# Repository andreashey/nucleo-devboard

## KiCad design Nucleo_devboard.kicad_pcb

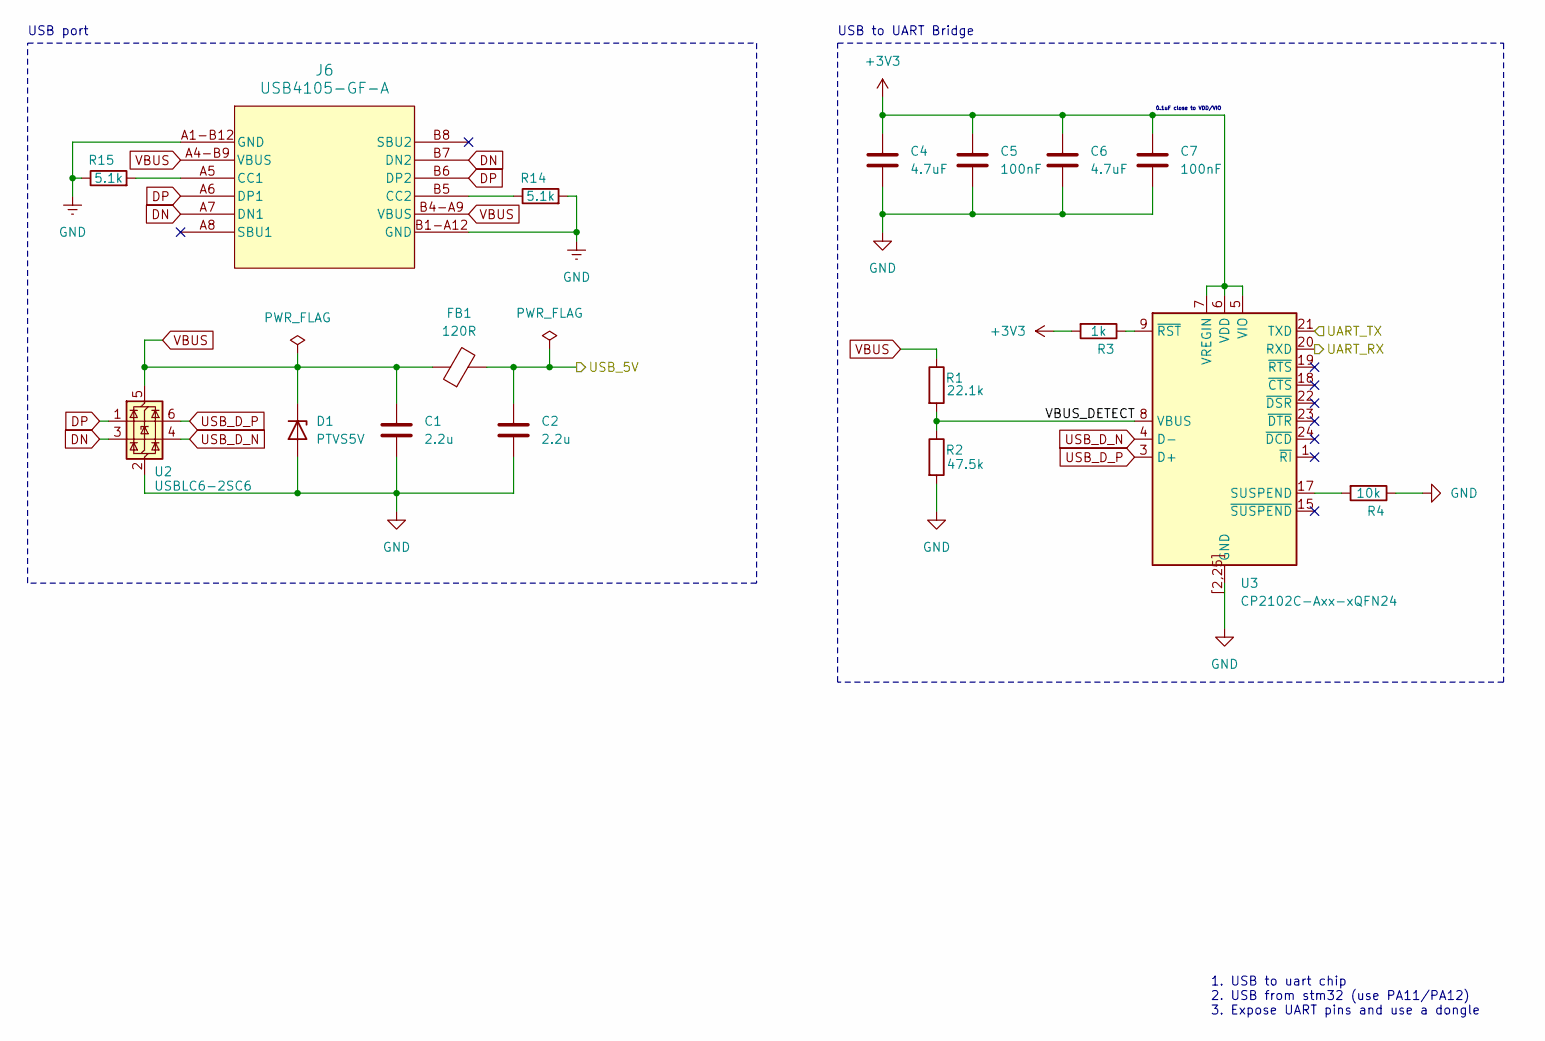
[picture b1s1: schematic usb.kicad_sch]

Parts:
C1, C2: 2.2u; C_0805_2012Metric
C4, C6: 4.7uF; C_0805_2012Metric
C5, C7: 100nF; C_0603_1608Metric
D1: PTVS5V; D_SOD-123
FB1: 120R; L_0805_2012Metric
J6: USB4105-GF-A; USB4105_GCT
R1: 22.1k; R_0603_1608Metric
R2: 47.5k; R_0603_1608Metric
R3: 1k; R_0805_2012Metric
R4: 10k; R_0805_2012Metric
R14, R15: 5.1k; R_0603_1608Metric
U2: USBLC6-2SC6; SOT-23-6
U3: CP2102C-Axx-xQFN24; WQFN-24-1EP_4x4mm_P0.5mm_EP2.45x2.45mm

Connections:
+3V3: C4.1, C5.1, C6.1, C7.1, R3.2, U3.5 (VIO), U3.6 (VDD), U3.7 (VREGIN); also elsewhere on the board
/MCU 1/USART3_RX: U3.20 (RXD); also elsewhere on the board
/MCU 1/USART3_TX: U3.21 (TXD); also elsewhere on the board
/Power/USB_5V: C2.1, FB1.2; also elsewhere on the board
/USB/VBUS_DETECT: R1.2, R2.1, U3.8 (VBUS)
DN: J6.A7 (DN1), J6.B7 (DN2), U2.3 (I/O2)
DP: J6.A6 (DP1), J6.B6 (DP2), U2.1 (I/O1)
GND: C1.2, C2.2, C4.2, C5.2, C6.2, C7.2, D1.2 (A), J6.A1-B12 (GND), J6.B1-A12 (GND), R2.2, R4.1, R14.2, R15.1, U2.2 (GND), U3.2 (GND), U3.25 (GND), U3.[2,25] (GND); also elsewhere on the board
unnamed: J6.A5 (CC1), R15.2
unnamed: J6.B5 (CC2), R14.1
unnamed: R4.2, U3.17 (SUSPEND)
unnamed: R3.1, U3.9 (~RST)
USB_D_N: U2.4 (I/O2), U3.4 (D-)
USB_D_P: U2.6 (I/O1), U3.3 (D+)
VBUS: C1.1, D1.1 (K), FB1.1, J6.A4-B9 (VBUS), J6.B4-A9 (VBUS), R1.1, U2.5 (VBUS)

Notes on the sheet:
1. USB to uart chip 2. USB from stm32 (use PA11/PA12) 3. Expose UART pins and use a dongle
USB to UART Bridge
USB port
0.1uF close to VDD/VIO

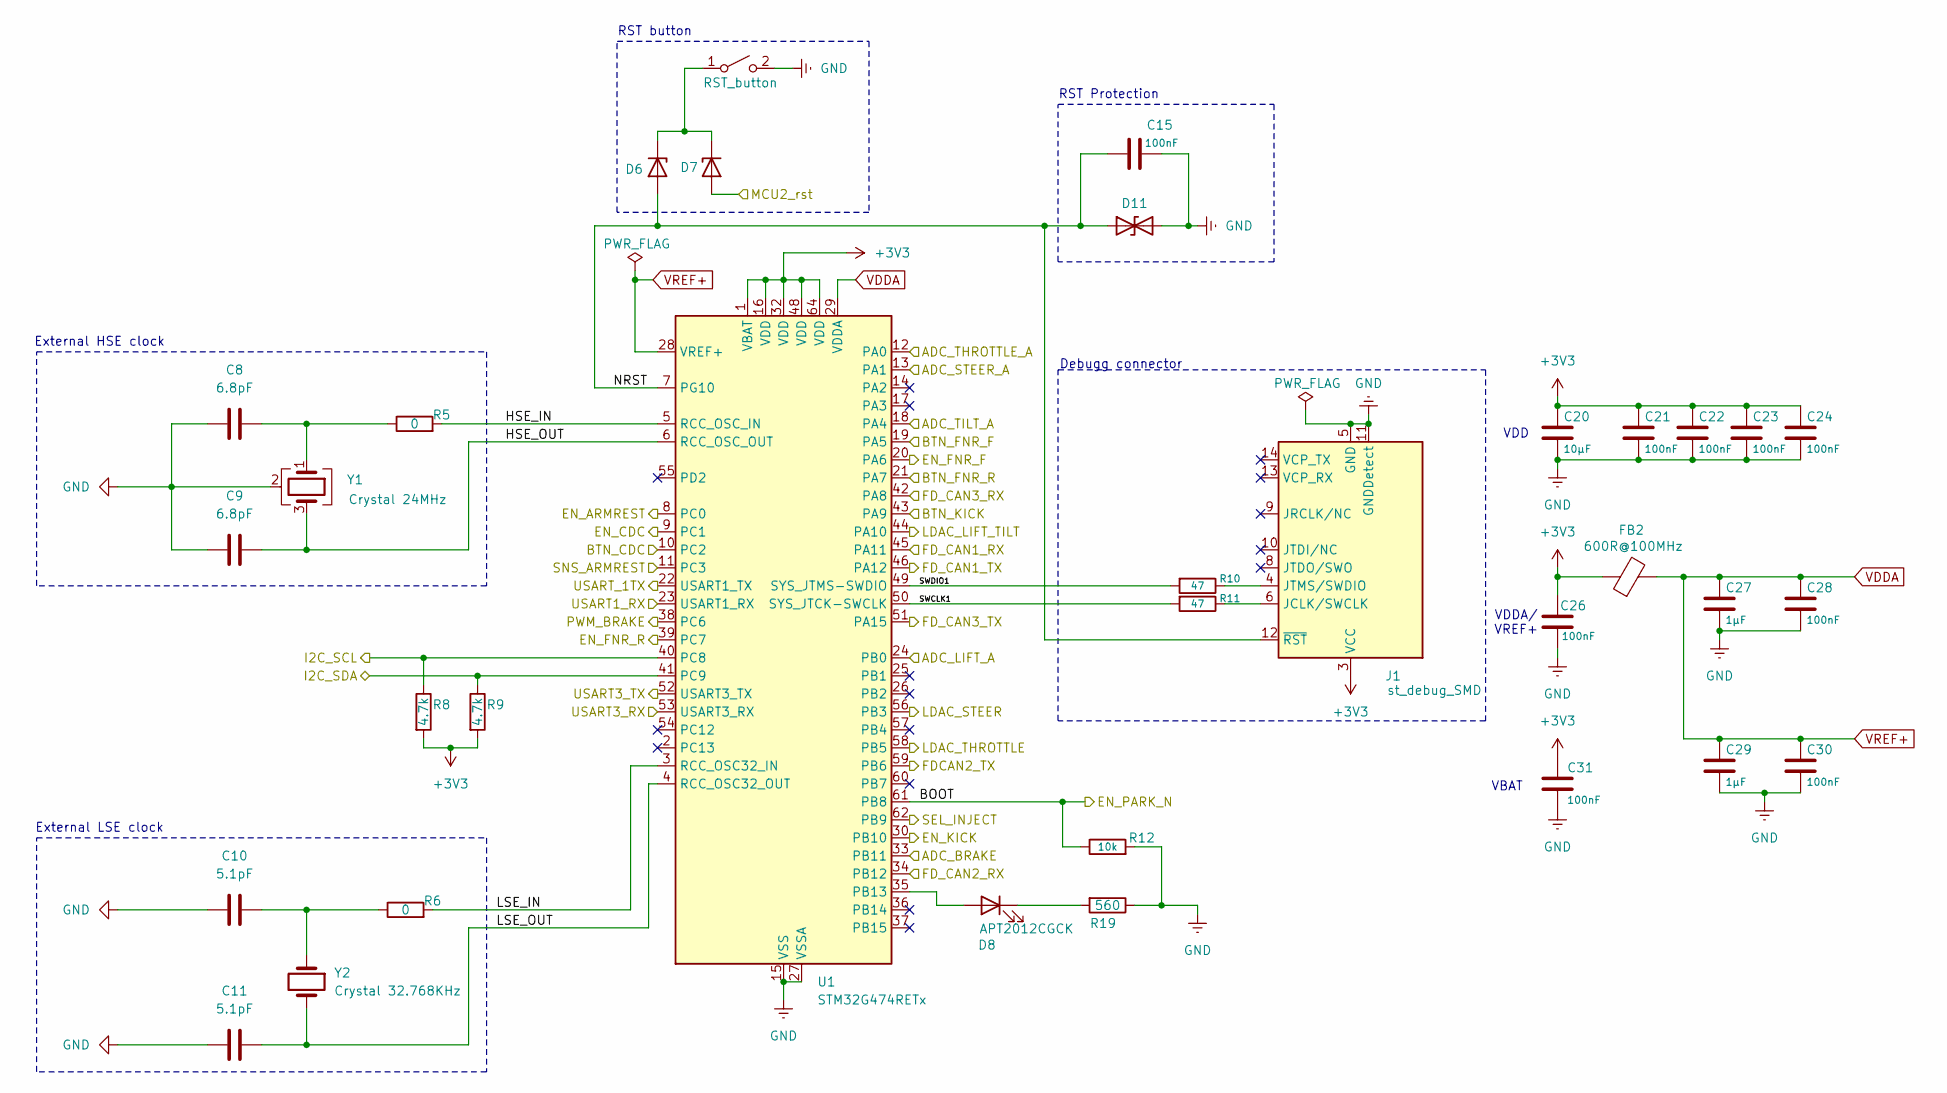
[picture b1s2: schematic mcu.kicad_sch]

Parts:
C8, C9: 6.8pF; C_0402_1005Metric
C10, C11: 5.1pF; C_0402_1005Metric
C15, C21, C22, C23, C24, C26, C28, C30, C31: 100nF; C_0603_1608Metric
C20: 10μF; C_1206_3216Metric
C27, C29: 1μF; C_0603_1608Metric
D6, D7: BAT60A; D_SOD-323
D8: APT2012CGCK; LED_0805_2012Metric
D11: STS321033B401; D_SOD-323
FB2: 600R@100MHz; L_0603_1608Metric
J1: st_debug_SMD; PinHeader_2x07_P1.27mm_Vertical_SMD
R5, R6: 0; R_0603_1608Metric
R8, R9: 4.7k; R_0805_2012Metric
R10, R11: 47; R_0603_1608Metric
R12: 10k; R_0805_2012Metric
R19: 560; R_0805_2012Metric
RESET1: RST_button; SW_TH_Tactile_Omron_B3F-100x
U1: STM32G474RETx; LQFP-64_10x10mm_P0.5mm
Y1: Crystal 24MHz; Crystal_SMD_2016-4Pin_2.0x1.6mm
Y2: Crystal 32.768KHz; Crystal_SMD_3215-2Pin_3.2x1.5mm

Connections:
+3V3: C20.1, C21.1, C22.1, C23.1, C24.1, C26.1, C31.1, FB2.1, J1.3 (VCC), R8.2, R9.2, U1.1 (VBAT), U1.16 (VDD), U1.32 (VDD), U1.48 (VDD), U1.64 (VDD); also elsewhere on the board
/MCU 1/ADC_BRAKE: U1.33 (PB11); also elsewhere on the board
/MCU 1/ADC_LIFT_A: U1.24 (PB0); also elsewhere on the board
/MCU 1/ADC_STEER_A: U1.13 (PA1); also elsewhere on the board
/MCU 1/ADC_THROTTLE_A: U1.12 (PA0); also elsewhere on the board
/MCU 1/ADC_TILT_A: U1.18 (PA4); also elsewhere on the board
/MCU 1/BOOT: R12.1, U1.61 (PB8); also elsewhere on the board
/MCU 1/BTN_CDC: U1.10 (PC2); also elsewhere on the board
/MCU 1/BTN_FNR_F: U1.19 (PA5); also elsewhere on the board
/MCU 1/BTN_FNR_R: U1.21 (PA7); also elsewhere on the board
/MCU 1/BTN_KICK: U1.43 (PA9); also elsewhere on the board
/MCU 1/EN_ARMREST: U1.8 (PC0); also elsewhere on the board
/MCU 1/EN_CDC: U1.9 (PC1); also elsewhere on the board
/MCU 1/EN_FNR_F: U1.20 (PA6); also elsewhere on the board
/MCU 1/EN_FNR_R: U1.39 (PC7); also elsewhere on the board
/MCU 1/EN_KICK: U1.30 (PB10); also elsewhere on the board
/MCU 1/FDCAN2_TX: U1.59 (PB6); also elsewhere on the board
/MCU 1/FD_CAN1_RX: U1.45 (PA11); also elsewhere on the board
/MCU 1/FD_CAN1_TX: U1.46 (PA12); also elsewhere on the board
/MCU 1/FD_CAN2_RX: U1.34 (PB12); also elsewhere on the board
/MCU 1/FD_CAN3_RX: U1.42 (PA8); also elsewhere on the board
/MCU 1/FD_CAN3_TX: U1.51 (PA15); also elsewhere on the board
/MCU 1/HSE_IN: R5.2, U1.5 (RCC_OSC_IN)
/MCU 1/HSE_OUT: C9.2, U1.6 (RCC_OSC_OUT), Y1.3
/MCU 1/I2C_SCL: R8.1, U1.40 (PC8); also elsewhere on the board
/MCU 1/I2C_SDA: R9.1, U1.41 (PC9); also elsewhere on the board
/MCU 1/LDAC_LIFT_TILT: U1.44 (PA10); also elsewhere on the board
/MCU 1/LDAC_STEER: U1.56 (PB3); also elsewhere on the board
/MCU 1/LDAC_THROTTLE: U1.58 (PB5); also elsewhere on the board
/MCU 1/LSE_IN: R6.2, U1.3 (RCC_OSC32_IN)
/MCU 1/LSE_OUT: C11.2, U1.4 (RCC_OSC32_OUT), Y2.2
/MCU 1/NRST: C15.1, D6.2 (A), D11.1 (A1), J1.12 (~RST), U1.7 (PG10)
/MCU 1/PWM_BRAKE: U1.38 (PC6); also elsewhere on the board
/MCU 1/SEL_INJECT: U1.62 (PB9); also elsewhere on the board
/MCU 1/SNS_ARMREST: U1.11 (PC3); also elsewhere on the board
/MCU 1/SWCLK1: R11.2, U1.50 (SYS_JTCK-SWCLK)
/MCU 1/SWDIO1: R10.2, U1.49 (SYS_JTMS-SWDIO)
/MCU 1/USART1_RX: U1.23 (USART1_RX); also elsewhere on the board
/MCU 1/USART3_RX: U1.53 (USART3_RX); also elsewhere on the board
/MCU 1/USART3_TX: U1.52 (USART3_TX); also elsewhere on the board
/MCU 1/USART_1TX: U1.22 (USART1_TX); also elsewhere on the board
/MCU 2/NRST: D7.2 (A); also elsewhere on the board
GND: C8.1, C9.1, C10.1, C11.1, C15.2, C20.2, C21.2, C22.2, C23.2, C24.2, C26.2, C27.2, C28.2, C29.2, C30.2, C31.2, D11.2 (A2), J1.5 (GND), J1.7 (GND), J1.11 (GNDDetect), R12.2, R19.1, RESET1.2 (B), U1.15 (VSS), U1.27 (VSSA), U1.31 (VSS), U1.47 (VSS), U1.63 (VSS), Y1.2 (G), Y1.4 (G); also elsewhere on the board
unnamed: C8.2, R5.1, Y1.1
unnamed: C10.2, R6.1, Y2.1
unnamed: D6.1 (K), D7.1 (K), RESET1.1 (A)
unnamed: D8.2 (A), U1.35 (PB13)
unnamed: D8.1 (K), R19.2
unnamed: J1.6 (JCLK/SWCLK), R11.1
unnamed: J1.4 (JTMS/SWDIO), R10.1
VDDA: C27.1, C28.1, C29.1, C30.1, FB2.2, U1.28 (VREF+), U1.29 (VDDA)

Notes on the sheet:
External LSE clock
VDDA/ VREF+
VBAT
VDD
RST Protection
RST button
External HSE clock
Debugg connector

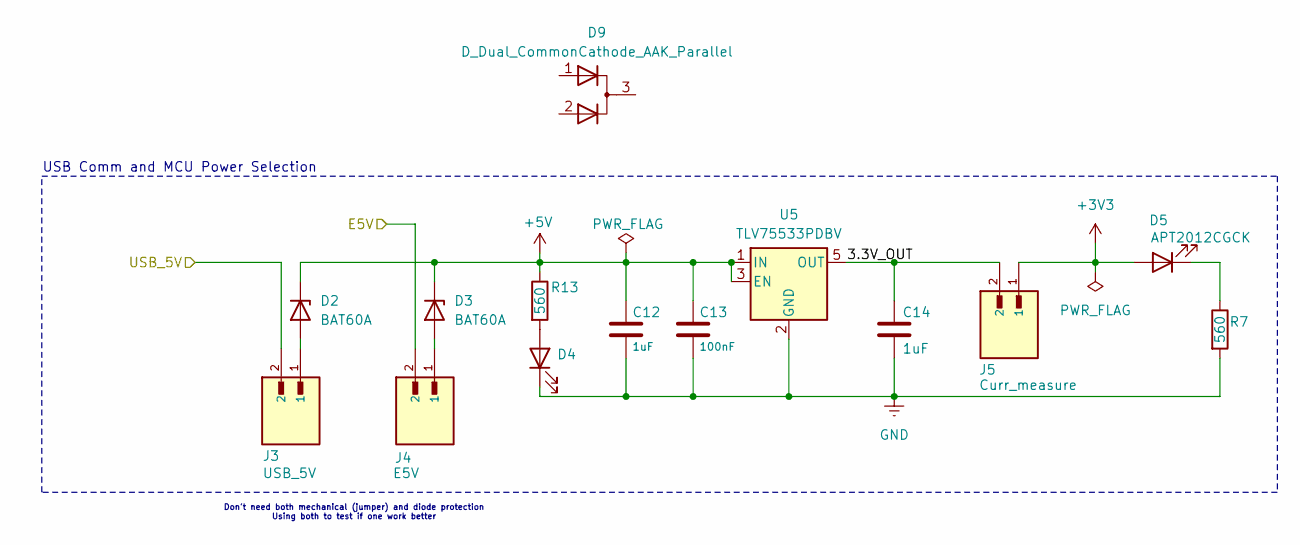
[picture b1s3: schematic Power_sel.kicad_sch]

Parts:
C12, C14: 1uF; C_0603_1608Metric
C13: 100nF; C_0603_1608Metric
D2, D3: BAT60A; D_SOD-323
D4, D5: APT2012CGCK; LED_0805_2012Metric
D9: D_Dual_CommonCathode_AAK_Parallel; SOT-23
J3: USB_5V; jumper_header; PARTREV 14
J4: E5V; jumper_header; PARTREV 14
J5: Curr_measure; jumper_header; PARTREV 14
R7, R13: 560; R_0805_2012Metric
U5: TLV75533PDBV; SOT-23-5

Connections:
+3V3: D5.2 (A), J5.1; also elsewhere on the board
+5V: C12.1, C13.1, D2.1 (K), D3.1 (K), R13.1, U5.1 (IN), U5.3 (EN); also elsewhere on the board
/Morpho connector/E5V: J4.2; also elsewhere on the board
/Power/3.3V_OUT: C14.1, J5.2, U5.5 (OUT)
/Power/USB_5V: J3.2; also elsewhere on the board
GND: C12.2, C13.2, C14.2, D4.1 (K), R7.2, U5.2 (GND); also elsewhere on the board
unnamed: D2.2 (A), J3.1
unnamed: D3.2 (A), J4.1
unnamed: D4.2 (A), R13.2
unnamed: D5.1 (K), R7.1

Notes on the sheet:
Don't need both mechanical (jumper) and diode protection Using both to test if one work better
USB Comm and MCU Power Selection

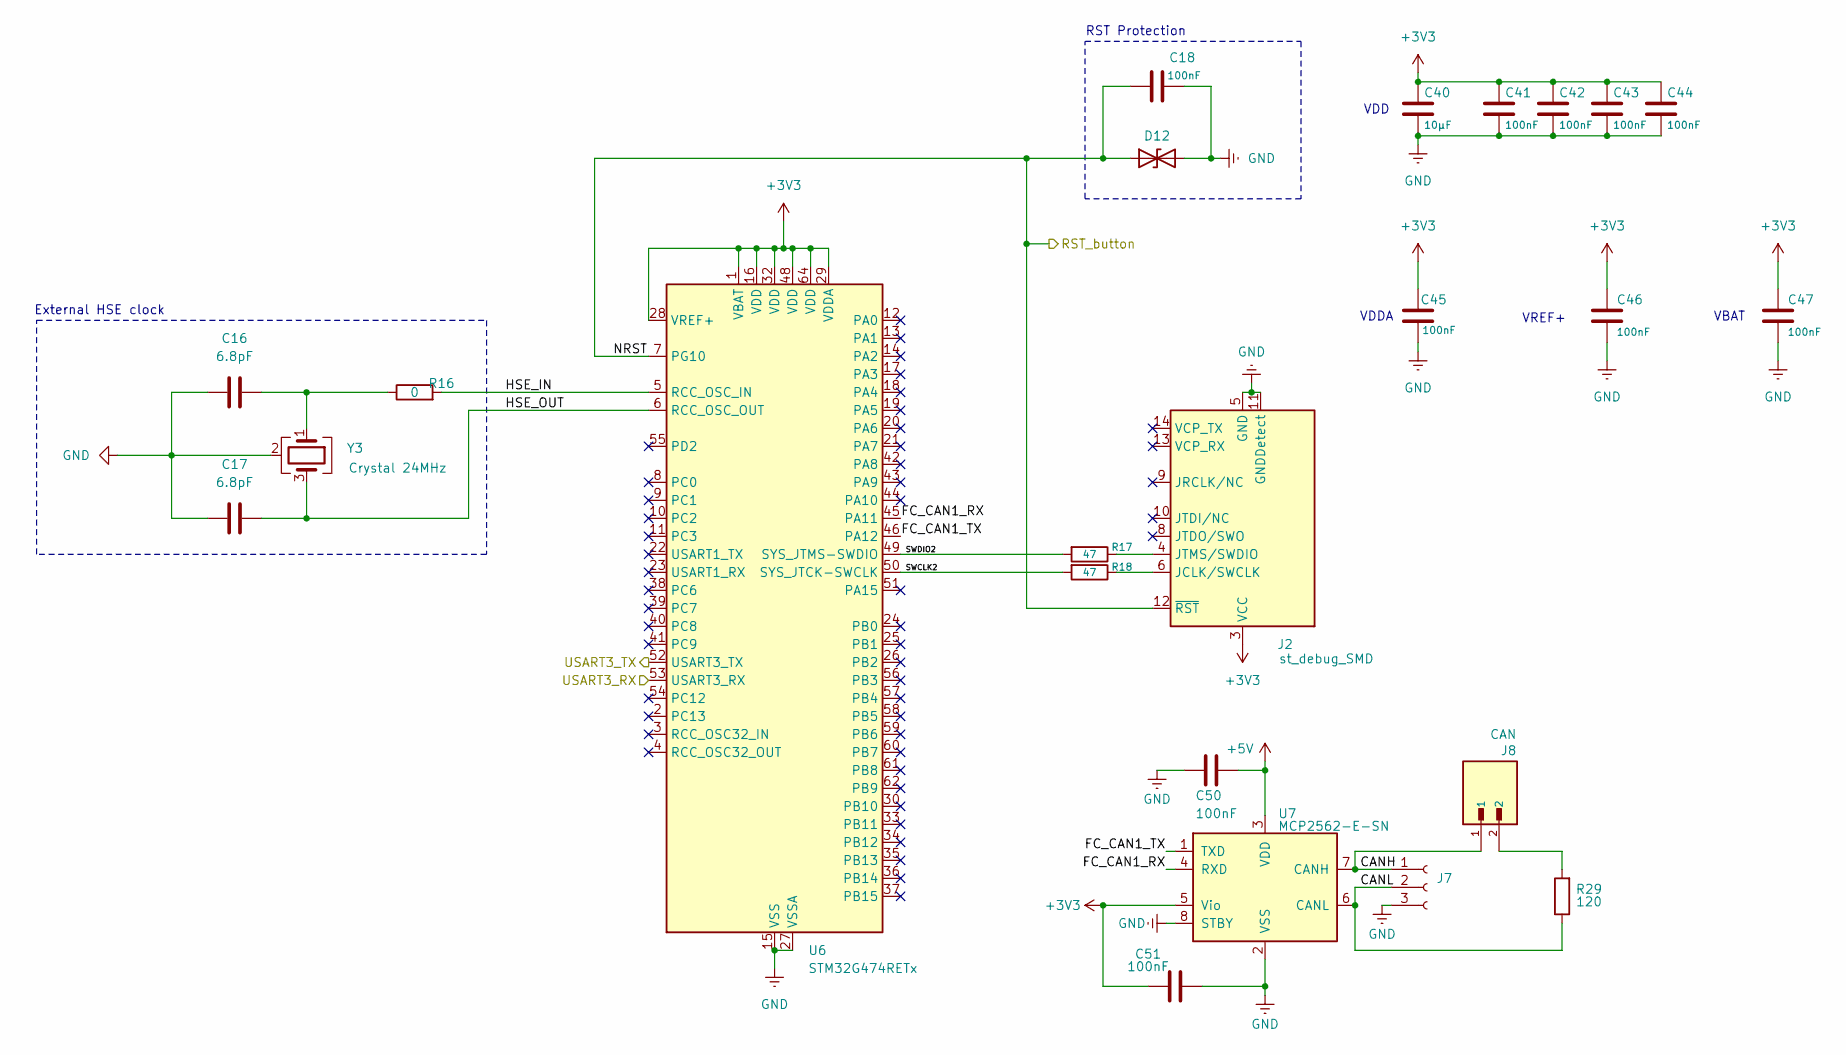
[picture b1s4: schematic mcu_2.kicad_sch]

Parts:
C16, C17: 6.8pF; C_0402_1005Metric
C18, C41, C42, C43, C44, C45, C46, C47, C50, C51: 100nF; C_0603_1608Metric
C40: 10μF; C_1206_3216Metric
D12: STS321033B401; D_SOD-323
J2: st_debug_SMD; PinHeader_2x07_P1.27mm_Vertical_SMD
J7: Conn_01x03_Socket; DF3-3P-2DSA
J8: CAN; jumper_header; PARTREV 14
R16: 0; R_0603_1608Metric
R17, R18: 47; R_0603_1608Metric
R29: 120; R_0805_2012Metric
U6: STM32G474RETx; LQFP-64_10x10mm_P0.5mm
U7: MCP2562-E-SN; SOIC-8_3.9x4.9mm_P1.27mm
Y3: Crystal 24MHz; Crystal_SMD_2016-4Pin_2.0x1.6mm

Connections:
+3V3: C40.1, C41.1, C42.1, C43.1, C44.1, C45.1, C46.1, C47.1, C51.1, J2.3 (VCC), U6.1 (VBAT), U6.16 (VDD), U6.28 (VREF+), U6.29 (VDDA), U6.32 (VDD), U6.48 (VDD), U6.64 (VDD), U7.5 (Vio); also elsewhere on the board
+5V: C50.2, U7.3 (VDD); also elsewhere on the board
/MCU 1/USART1_RX: U6.52 (USART3_TX); also elsewhere on the board
/MCU 1/USART_1TX: U6.53 (USART3_RX); also elsewhere on the board
/MCU 2/CANH: J7.1, J8.1, U7.7 (CANH)
/MCU 2/CANL: J7.2, R29.1, U7.6 (CANL)
/MCU 2/FC_CAN1_RX: U6.45 (PA11), U7.4 (RXD)
/MCU 2/FC_CAN1_TX: U6.46 (PA12), U7.1 (TXD)
/MCU 2/HSE_IN: R16.2, U6.5 (RCC_OSC_IN)
/MCU 2/HSE_OUT: C17.2, U6.6 (RCC_OSC_OUT), Y3.3
/MCU 2/NRST: C18.1, D12.1 (A1), J2.12 (~RST), U6.7 (PG10); also elsewhere on the board
/MCU 2/SWCLK2: R18.2, U6.50 (SYS_JTCK-SWCLK)
/MCU 2/SWDIO2: R17.2, U6.49 (SYS_JTMS-SWDIO)
GND: C16.1, C17.1, C18.2, C40.2, C41.2, C42.2, C43.2, C44.2, C45.2, C46.2, C47.2, C50.1, C51.2, D12.2 (A2), J2.5 (GND), J2.7 (GND), J2.11 (GNDDetect), J7.3, U6.15 (VSS), U6.27 (VSSA), U6.31 (VSS), U6.47 (VSS), U6.63 (VSS), U7.2 (VSS), U7.8 (STBY), Y3.2 (G), Y3.4 (G); also elsewhere on the board
unnamed: C16.2, R16.1, Y3.1
unnamed: J2.6 (JCLK/SWCLK), R18.1
unnamed: J2.4 (JTMS/SWDIO), R17.1
unnamed: J8.2, R29.2

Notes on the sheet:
VREF+
External HSE clock
RST Protection
VBAT
VDD
VDDA

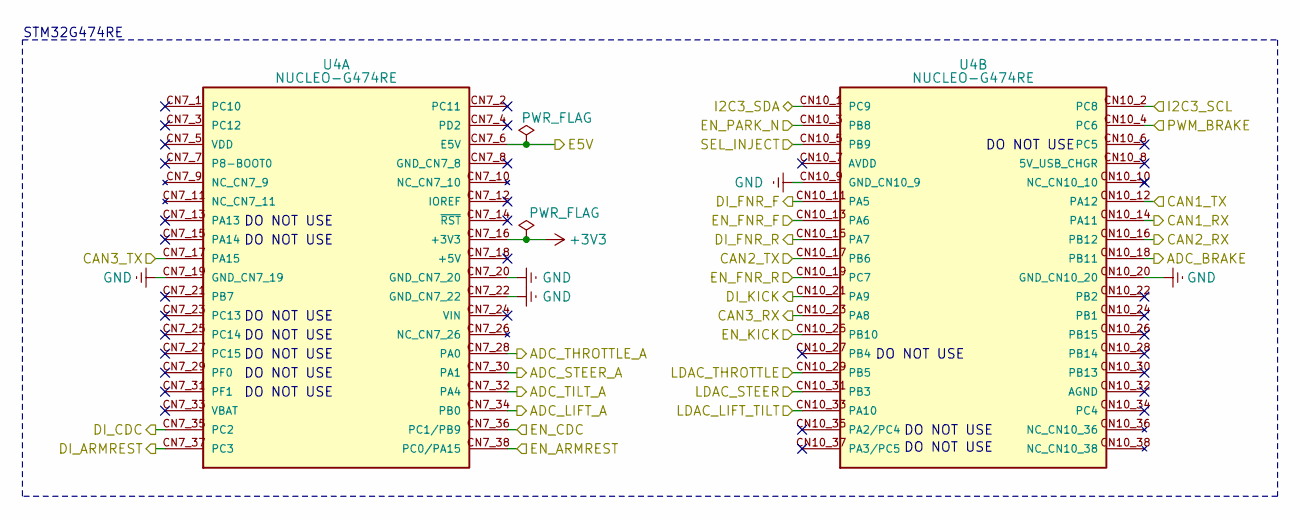
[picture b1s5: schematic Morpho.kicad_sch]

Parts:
U4: NUCLEO-G474RE; MODULE_NUCLEO-G474RE; PARTREV 17

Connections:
+3V3: U4.CN7_16 (+3V3); also elsewhere on the board
/MCU 1/ADC_BRAKE: U4.CN10_18 (PB11); also elsewhere on the board
/MCU 1/ADC_LIFT_A: U4.CN7_34 (PB0); also elsewhere on the board
/MCU 1/ADC_STEER_A: U4.CN7_30 (PA1); also elsewhere on the board
/MCU 1/ADC_THROTTLE_A: U4.CN7_28 (PA0); also elsewhere on the board
/MCU 1/ADC_TILT_A: U4.CN7_32 (PA4); also elsewhere on the board
/MCU 1/BOOT: U4.CN10_3 (PB8); also elsewhere on the board
/MCU 1/BTN_CDC: U4.CN7_35 (PC2); also elsewhere on the board
/MCU 1/BTN_FNR_F: U4.CN10_11 (PA5); also elsewhere on the board
/MCU 1/BTN_FNR_R: U4.CN10_15 (PA7); also elsewhere on the board
/MCU 1/BTN_KICK: U4.CN10_21 (PA9); also elsewhere on the board
/MCU 1/EN_ARMREST: U4.CN7_38 (PC0/PA15); also elsewhere on the board
/MCU 1/EN_CDC: U4.CN7_36 (PC1/PB9); also elsewhere on the board
/MCU 1/EN_FNR_F: U4.CN10_13 (PA6); also elsewhere on the board
/MCU 1/EN_FNR_R: U4.CN10_19 (PC7); also elsewhere on the board
/MCU 1/EN_KICK: U4.CN10_25 (PB10); also elsewhere on the board
/MCU 1/FDCAN2_TX: U4.CN10_16 (PB12); also elsewhere on the board
/MCU 1/FD_CAN1_RX: U4.CN10_14 (PA11); also elsewhere on the board
/MCU 1/FD_CAN1_TX: U4.CN10_12 (PA12); also elsewhere on the board
/MCU 1/FD_CAN2_RX: U4.CN10_17 (PB6); also elsewhere on the board
/MCU 1/FD_CAN3_RX: U4.CN10_23 (PA8); also elsewhere on the board
/MCU 1/FD_CAN3_TX: U4.CN7_17 (PA15); also elsewhere on the board
/MCU 1/I2C_SCL: U4.CN10_2 (PC8); also elsewhere on the board
/MCU 1/I2C_SDA: U4.CN10_1 (PC9); also elsewhere on the board
/MCU 1/LDAC_LIFT_TILT: U4.CN10_33 (PA10); also elsewhere on the board
/MCU 1/LDAC_STEER: U4.CN10_31 (PB3); also elsewhere on the board
/MCU 1/LDAC_THROTTLE: U4.CN10_29 (PB5); also elsewhere on the board
/MCU 1/PWM_BRAKE: U4.CN10_4 (PC6); also elsewhere on the board
/MCU 1/SEL_INJECT: U4.CN10_5 (PB9); also elsewhere on the board
/MCU 1/SNS_ARMREST: U4.CN7_37 (PC3); also elsewhere on the board
/Morpho connector/E5V: U4.CN7_6 (E5V); also elsewhere on the board
GND: U4.CN7_19 (GND_CN7_19), U4.CN7_20 (GND_CN7_20), U4.CN7_22 (GND_CN7_22), U4.CN10_9 (GND_CN10_9), U4.CN10_20 (GND_CN10_20); also elsewhere on the board

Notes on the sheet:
DO NOT USE
STM32G474RE

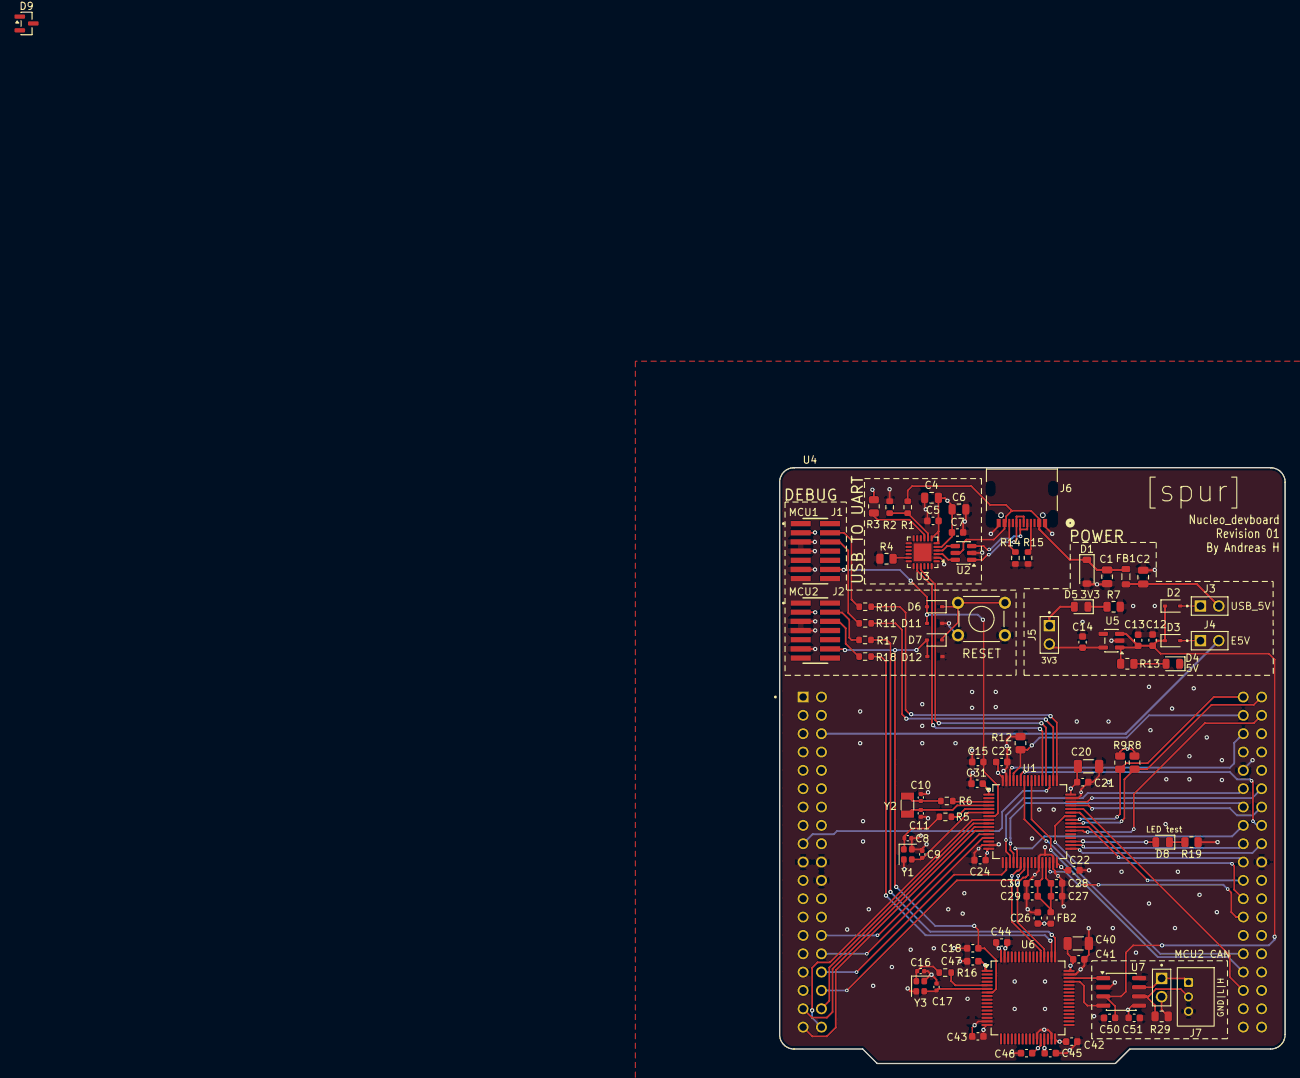
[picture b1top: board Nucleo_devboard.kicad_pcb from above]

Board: 4 copper layers, 70.0 x 82.5 mm, 90 parts (0 on the bottom side), 81 nets.
